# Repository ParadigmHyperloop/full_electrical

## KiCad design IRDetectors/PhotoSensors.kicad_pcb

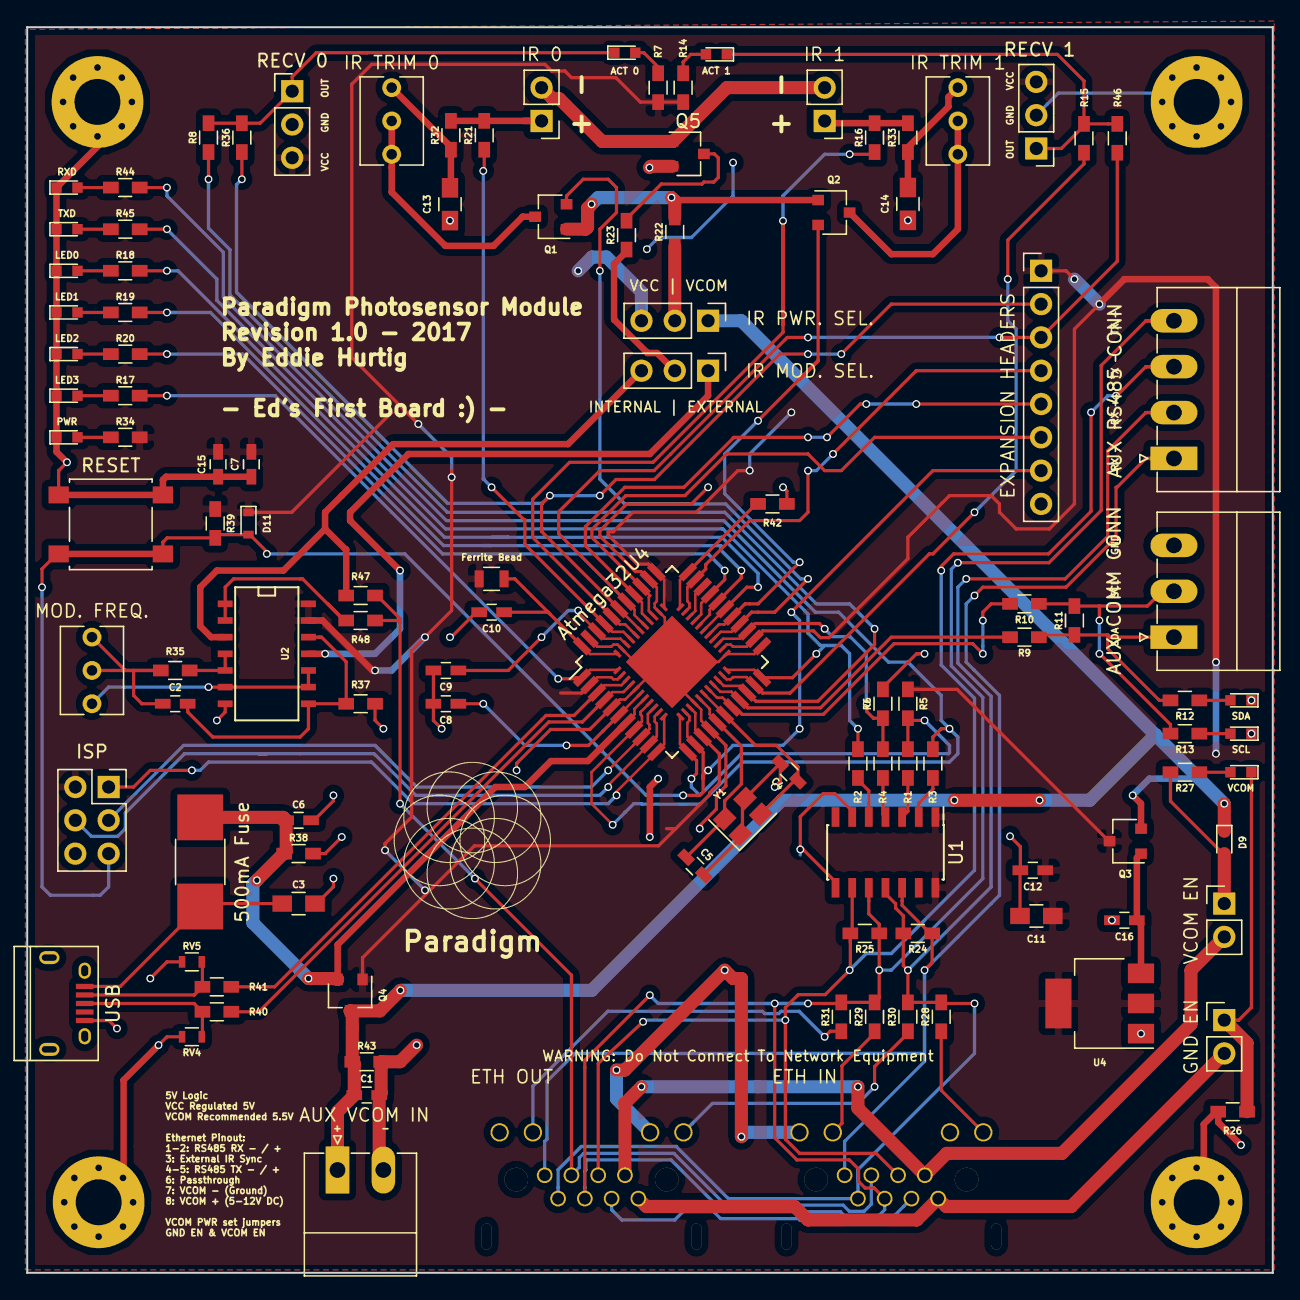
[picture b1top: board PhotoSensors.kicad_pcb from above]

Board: 2 copper layers, 95.0 x 95.0 mm, 112 parts (0 on the bottom side), 92 nets.

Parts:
500mA Fuse: 500mA; R_1812_HandSoldering
ACT 0: D0_ACT; LED_0603
ACT 1: D1_ACT; LED_0603
AUX COMM CONN: I2C _CONN; PhoenixContact_MC-G_03x3.50mm_Angled
AUX RS485 CONN: RS485_CONN; PhoenixContact_MC-G_04x3.50mm_Angled
AUX VCOM IN: PWR_IN; PhoenixContact_MC-G_02x3.50mm_Angled
Atmega32U4: ATMEGA32U4RC-A; QFN-44_7x7mm_Combined_TQFP-44_10x10mm_Pitch0.8mm
C1, C2: 10n; C_0603_HandSoldering
C3, C11: 22u; C_0805_HandSoldering
C4, C5: 22p; C_0603_HandSoldering
C6, C7, C9, C12, C15, C16: 100n; C_0603_HandSoldering
C8, C10: 1u; C_0603_HandSoldering
C13, C14: 10u; C_0805_HandSoldering
D9: D_VCOM; D_0603
D11: D_RST; D_0603
EXPANSION HEADERS: CONN_01X08; Pin_Header_Straight_1x08_Pitch2.54mm
Ferrite Bead: Ferrite_Bead; R_0805
GND EN: GND_EN; Pin_Header_Straight_1x02_Pitch2.54mm
IR 0: CONN_IR0; Pin_Header_Straight_1x02_Pitch2.54mm
IR 1: CONN_IR1; Pin_Header_Straight_1x02_Pitch2.54mm
IR MOD. SEL.: IR_SYNC_SELECT; Pin_Header_Straight_1x03_Pitch2.54mm
IR PWR. SEL.: Emitter Current Source; Pin_Header_Straight_1x03_Pitch2.54mm
IR TRIM 0, IR TRIM 1: RP500; Potentiometer_Trimmer_Vishay_T73XW_Vertical
ISP: ISP; Socket_Strip_Straight_2x03_Pitch2.54mm
J1, J2: RJ45_LEDS; RJ45_8P8C_90DEG_LEDs
LED0: LED1; LED_0603
LED1: LED2; LED_0603
LED2: LED3; LED_0603
LED3: LED0; LED_0603
MOD. FREQ.: POT_TRIM; Potentiometer_Trimmer_Vishay_T73XW_Vertical
PWR: PWR_LED; LED_0603
Q1, Q2, Q4: FDN340PCT-ND; SC-59
Q3: FDN340PCT; SC-59
Q5: Q_PMOS_SDG; SC-59
R1, R2, R3, R4, R16, R21, R23, R26, R32, R33, R36, R46, R48: 0; R_0603_HandSoldering
R5, R6: 20k; R_0603_HandSoldering
R7, R12, R13, R14, R17, R18, R19, R20, R27, R28, R29, R30, R31, R34, R44, R45: 1k; R_0603_HandSoldering
R8, R15: 220; R_0603_HandSoldering
R9, R10, R11, R47: DNS; R_0603_HandSoldering
R22: 470; R_0603_HandSoldering
R24, R25: 120; R_0603_HandSoldering
R35: 100k; R_0603_HandSoldering
R37, R38, R39, R42, R43: 10k; R_0603_HandSoldering
R40, R41: 22R; R_0603_HandSoldering
RECV 0: CONN_PD0; Pin_Header_Straight_1x03_Pitch2.54mm
RECV 1: CONN_PD1; Pin_Header_Straight_1x03_Pitch2.54mm
RESET: RESET_BTN; SW_SPST_B3S-1000
RV4, RV5: CG0603MLC; R_0603
RXD: RX_LED; LED_0603
SCL: SCL; LED_0603
SDA: SDA; LED_0603
TXD: TX_LED; LED_0603
U1: MAX13432EETD; SOIC-14_3.9x8.7mm_Pitch1.27mm
U2: 7400; SOIC-14_N
U4: NCP1117ST50T3GOSCT; SOT-223
USB: USB_MICRO; USB_Micro-B
VCOM: VCOM_PWR; LED_0603
VCOM EN: VCOM_EN; Pin_Header_Straight_1x02_Pitch2.54mm
Y1: Crystal; Crystal_SMD_Abracon_ABM8G-4pin_3.2x2.5mm

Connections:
/ADC4: Atmega32U4.39, EXPANSION HEADERS.2, R36.1
/ADC5: Atmega32U4.38, EXPANSION HEADERS.3, R46.1
/Atmega/D+: Atmega32U4.4, R40.1
/Atmega/D-: Atmega32U4.3, R41.1
/Atmega/MISO: Atmega32U4.11, ISP.1
/Atmega/MOSI: Atmega32U4.10, ISP.4
/Atmega/PC7: Atmega32U4.32, EXPANSION HEADERS.4
/Atmega/PF6: Atmega32U4.37, EXPANSION HEADERS.5
/Atmega/PF7: Atmega32U4.36, EXPANSION HEADERS.6
/Atmega/SCK: Atmega32U4.9, ISP.3
/Atmega/XTAL1: Atmega32U4.17, C4.1, Y1.2
/Atmega/XTAL2: Atmega32U4.16, C5.1, Y1.4
/D0_OUT: ACT 0.1, R8.2, R36.2, RECV 0.1
/D1_OUT: ACT 1.1, R15.2, R46.2, RECV 1.1
/DE: Atmega32U4.12, R1.1, R5.1
/EXT_SYNC: J1.3, J2.3, R47.1, R48.1
/INT0: Atmega32U4.20, R8.1
/INT1: Atmega32U4.21, R15.1
/IR0_+: IR 0.1, R21.2, R32.2
/IR0_-: IR 0.2, IR 1.2, Q5.1
/IR0_ADC: Atmega32U4.41, R21.1
/IR0_SETPOINT: Atmega32U4.26, Q1.2
/IR1_+: IR 1.1, R16.1, R33.2
/IR1_ADC: Atmega32U4.40, R16.2
/IR1_SETPOINT: Atmega32U4.27, Q2.2
/LED0: Atmega32U4.1, R17.2
/LED1: Atmega32U4.28, R18.2
/LED2: Atmega32U4.29, R19.2
/LED3: Atmega32U4.30, R20.2
/RE: Atmega32U4.25, R4.1, R6.2
/RESET: Atmega32U4.13, D11.2, EXPANSION HEADERS.7, ISP.5, R39.2, RESET.2
/RS422_Transiever/DE: R1.2, U1.3
/RS422_Transiever/RE: R4.2, U1.4
/RS422_Transiever/RS485_RX_+: AUX RS485 CONN.2, J1.2, J2.2, R24.1, R28.2, R30.2, U1.11
/RS422_Transiever/RS485_RX_-: AUX RS485 CONN.1, J1.1, J2.1, R24.2, U1.12
/RS422_Transiever/RS485_TX_+: AUX RS485 CONN.4, J1.4, J2.4, R25.1, R29.2, R31.2, U1.10
/RS422_Transiever/RS485_TX_-: AUX RS485 CONN.3, J1.5, J2.5, R25.2, U1.9
/RS422_Transiever/RXD: R3.2, U1.2
/RS422_Transiever/TXD: R2.2, U1.5
/RXD: Atmega32U4.8, R3.1, R44.2
/SCL: Atmega32U4.18, R10.2
/SDA: Atmega32U4.19, R9.2
/TXD: Atmega32U4.22, R2.1, R45.2
GND: AUX COMM CONN.3, AUX VCOM IN.2, Atmega32U4.5, Atmega32U4.15, Atmega32U4.23, Atmega32U4.35, Atmega32U4.43, C1.2, C3.2, C4.2, C5.2, C6.2, C7.1, C8.2, C9.2, C10.2, C11.2, C12.2, C13.1, C14.1, C15.1, C16.2, EXPANSION HEADERS.8, ISP.6, J1.9, J1.11, J2.9, J2.11, LED0.1, LED1.1, LED2.1, LED3.1, PWR.1, Q5.2, R6.1, R26.2, R37.2, R38.2, R42.1, R43.1, RECV 0.2, RECV 1.2, RESET.1, RV4.1, RV5.1, RXD.1, SCL.1, SDA.1, TXD.1, U1.6, U1.8, U2.7, U4.1, USB.5, USB.6, Y1.1, Y1.3
unnamed: C2.1, MOD. FREQ..1, MOD. FREQ..2, R35.1
unnamed: C2.2, R37.1, U2.8, U2.12
unnamed: 500mA Fuse.2, C3.1, USB.1
unnamed: Atmega32U4.6, C8.1
unnamed: Atmega32U4.42, C9.1
unnamed: Atmega32U4.44, C10.1, Ferrite Bead.1
unnamed: C13.2, IR TRIM 0.3, R32.1
unnamed: C14.2, IR TRIM 1.3, R33.1
unnamed: C16.1, Q3.1, U4.3
unnamed: ACT 0.2, R7.2
unnamed: R12.2, SDA.2
unnamed: R13.2, SCL.2
unnamed: ACT 1.2, R14.2
unnamed: LED3.2, R17.1
unnamed: LED0.2, R18.1
unnamed: LED1.2, R19.1
unnamed: LED2.2, R20.1
unnamed: D9.2, R27.2, VCOM EN.1
unnamed: GND EN.1, R26.1, VCOM.1
unnamed: R27.1, VCOM.2
unnamed: PWR.2, R34.1
unnamed: R44.1, RXD.2
unnamed: R45.1, TXD.2
unnamed: MOD. FREQ..3, U2.6, U2.9, U2.10
unnamed: J1.7, J2.7, VCOM EN.2
unnamed: GND EN.2, J1.8, J2.8
unnamed: J1.10, R29.1
unnamed: J1.12, R28.1
unnamed: J2.10, R31.1
unnamed: J2.12, R30.1
unnamed: IR PWR. SEL..2, R22.1
unnamed: IR MOD. SEL..1, U2.11
unnamed: IR MOD. SEL..2, R23.1
unnamed: IR MOD. SEL..3, R47.2, U2.3
unnamed: AUX COMM CONN.1, R9.1, R11.1, R12.1
unnamed: AUX COMM CONN.2, R10.1, R11.2, R13.1
unnamed: R41.2, RV5.2, USB.2
unnamed: R40.2, RV4.2, USB.3
unnamed: Q1.1, Q2.1, R22.2
unnamed: IR TRIM 0.1, IR TRIM 0.2, Q1.3
unnamed: IR TRIM 1.1, IR TRIM 1.2, Q2.3
unnamed: Q5.3, R23.2
unnamed: R35.2, U2.4, U2.5
unnamed: Atmega32U4.33, R42.2
unnamed: R48.2, U2.1, U2.2
VCC: Atmega32U4.2, Atmega32U4.14, Atmega32U4.24, Atmega32U4.34, C7.2, C11.1, C12.1, C15.2, D11.1, EXPANSION HEADERS.1, Ferrite Bead.2, IR PWR. SEL..3, ISP.2, Q3.3, Q4.1, R5.2, R7.1, R14.1, R34.2, R39.1, RECV 0.3, RECV 1.3, U1.1, U1.14, U2.13, U2.14, U4.2, U4.4
VCOM: AUX VCOM IN.1, C1.1, D9.1, IR PWR. SEL..1, Q3.2, Q4.3, R43.2
VUSB: 500mA Fuse.1, Atmega32U4.7, C6.1, Q4.2, R38.1
